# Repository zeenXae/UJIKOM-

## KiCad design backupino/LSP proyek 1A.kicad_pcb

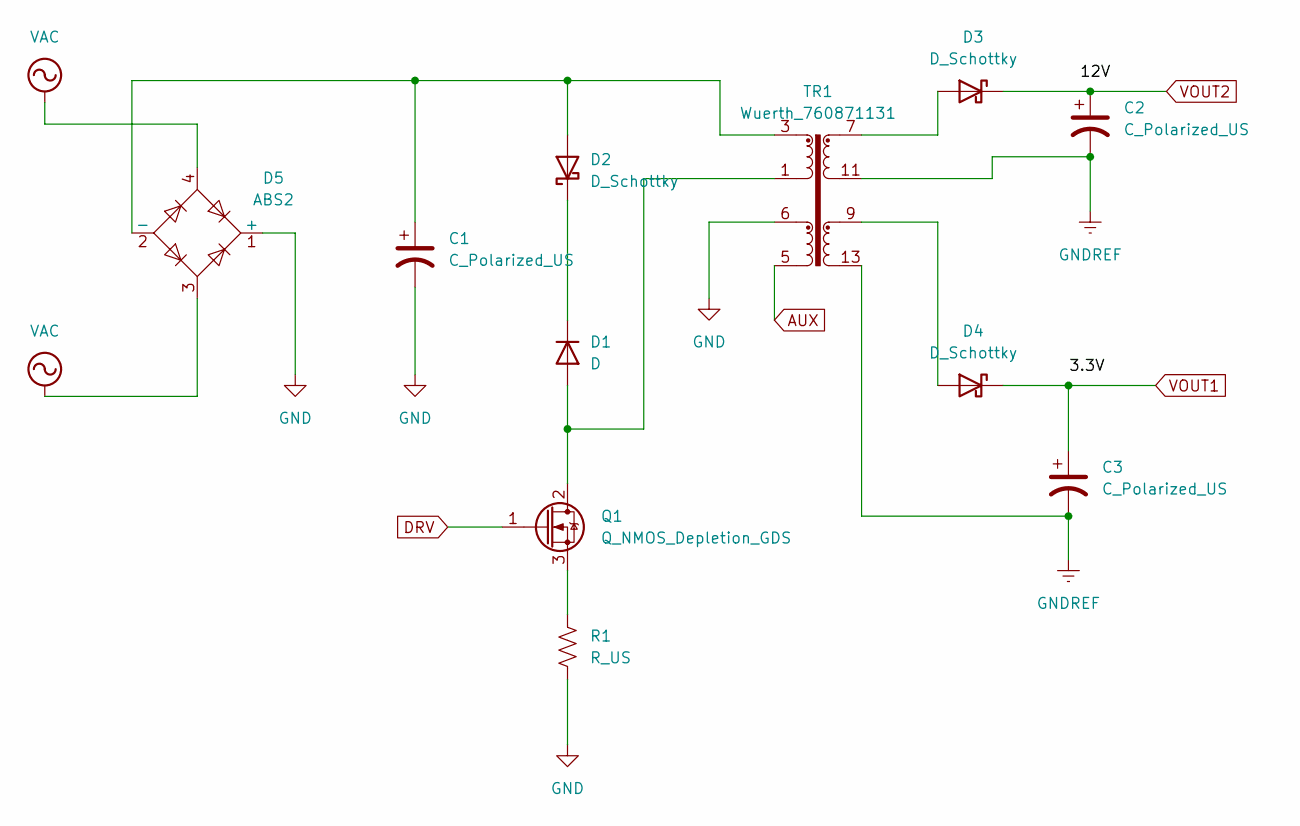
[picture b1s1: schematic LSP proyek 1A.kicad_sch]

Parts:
C1, C2, C3: C_Polarized_US; C_Axial_L12.0mm_D7.5mm_P15.00mm_Horizontal
D1: D; D_5KPW_P7.62mm_Vertical_AnodeUp
D2, D3, D4: D_Schottky; D_5KPW_P7.62mm_Vertical_AnodeUp
D5: ABS2; Diode_Bridge_Diotec_ABS
Q1: Q_NMOS_Depletion_GDS; SuperSOT-3
R1: R_US; R_Axial_DIN0204_L3.6mm_D1.6mm_P5.08mm_Horizontal
TR1: Wuerth_760871131; Transformer_Wuerth_760871131

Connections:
AUX: TR1.5
DRV: Q1.1 (G)
GND: C1.2, D5.1 (+), R1.2, TR1.6
GNDREF: C2.2, C3.2, TR1.11, TR1.12, TR1.13, TR1.14
unnamed: D1.2 (A), Q1.2 (D), TR1.1
unnamed: D1.1 (K), D2.1 (K)
unnamed: C1.1, D2.2 (A), D5.2 (-), TR1.3
unnamed: D3.2 (A), TR1.7, TR1.8
unnamed: D4.2 (A), TR1.9, TR1.10
unnamed: Q1.3 (S), R1.1
VAC: D5.3, D5.4
VOUT1: C3.1, D4.1 (K)
VOUT2: C2.1, D3.1 (K)

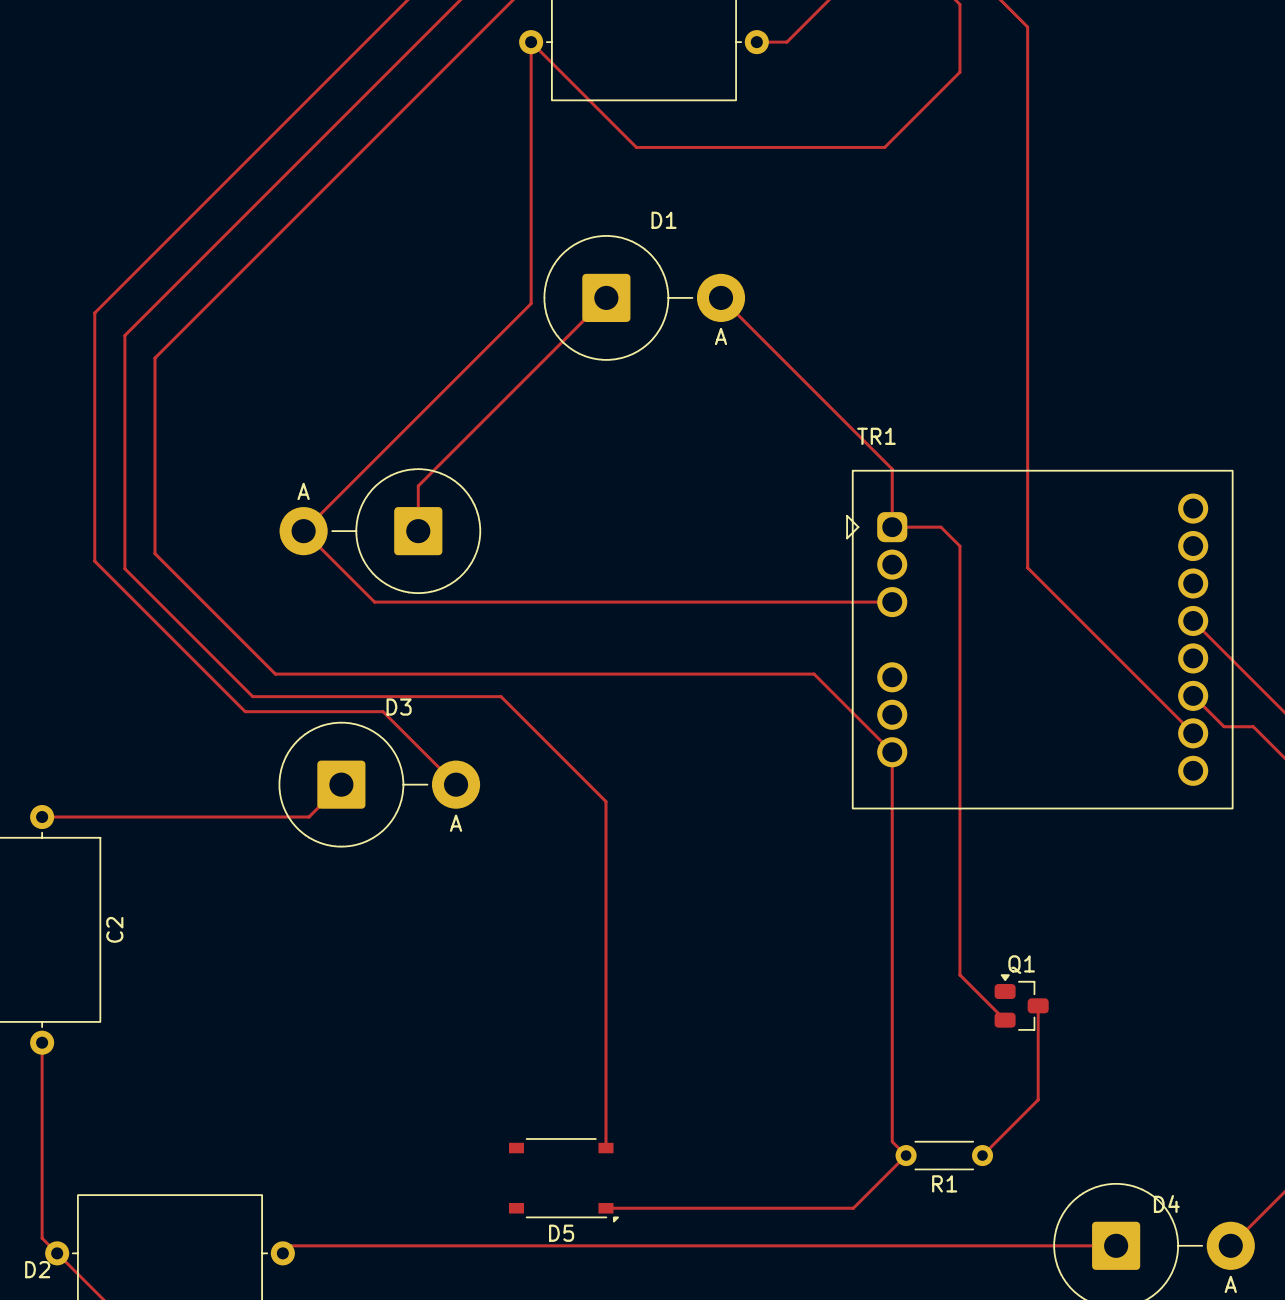
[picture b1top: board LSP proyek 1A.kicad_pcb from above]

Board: 2 copper layers, 11 parts (0 on the bottom side), 11 nets.
